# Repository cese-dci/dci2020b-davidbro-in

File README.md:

!!! important "Trabajo en progreso"
    Compruebe frecuentemente los cambios. Puedes aprovechar también 
    [**configurando las notificaciones de _release_**](https://docs.gitlab.com/ee/user/profile/notifications.html) 
    para [el repositorio](https://gitlab.com/FreeRTLS/FreeRTLS-Beacon/FreeRTLS-Beacon-Electronics) para estar enterado cuando 
    se realiza un nuevo lanzamiento.

# Bienvenido a FreeRTLS Beacon Electronics
**FreeRTLS Beacon Electronics** es una baliza UWB, _Open Source_, basada en el módulo
[DWM1001C](https://www.decawave.com/product/dwm1001-module/) de [Quorvo (antes Decawave)](https://www.decawave.com/). 

El desarrollo de este proyecto persigue los siguientes objetivos:

- Ser una versión de producción de [DWM1001 _development board_](https://www.decawave.com/product/dwm1001-development-board/)

Al igual que la original placa de desarrollo, posee las siguientes características[@dwm1001dev]:

- Soporte para UWB y _Bluetooth_
- Interfaz J-Link en la placa para grabar y depurar _firmware_
- Alimentación a través de micro USB

[Aquí](docs/requirements/index.md#por-que-hacerlo) se puede leer más sobre la motivación 
por la cuál se empezó con este proyecto.

La [documentación sobre la arquitectura](docs/architecture/index.md) permite entender cómo
está compuesto el sistema y cómo interactuán entre sí sus componentes. Cabe mencionar que 
**FreeRTLS Beacon Electronics** está formado por:

- Módulo [DWM1000C](https://www.decawave.com/product/dwm1001-module/)
- Interfaz J-Link implementada sobre 
[STM32F072CBTx](https://www.st.com/resource/en/datasheet/stm32f072c8.pdf)
- Fuente de alimentación a través de microUSB

### Misión
**FreeRTLS Beacon Electronics** busca permitir la implementación de sistemas de
localización en interiores, como es **FreeRTLS** pero no limitado a él. Es un _beacon_
UWB _open source_ y listo para fabricar o mejorar.

## Novedades
Para la lista completa de cambios visita el [control de cambios](CHANGELOG.md).

## ¿Cómo obtenerlo?
En la sección [_releases_](https://gitlab.com/FreeRTLS/FreeRTLS-Beacon/FreeRTLS-Beacon-Electronics/-/releases) del 
[repositorio](https://gitlab.com/FreeRTLS/FreeRTLS-Beacon/FreeRTLS-Beacon-Electronics) se pueden ver las versiones y el 
procedimiento para obtener **FreeRTLS Beacon Electronics**.

## ¿Cómo usarlo?
### Documentación
En la [documentación detallada](https://freertls.gitlab.io/FreeRTLS-Beacon/FreeRTLS-Beacon-Electronics) se encuentra todo
lo necesario para conocer cómo utilizar **FreeRTLS Beacon Electronics**.

## Contacto
Si quieres contactarme puedes hacerlo a davidmbroin@gmail.com.

## Licencia
Este proyecto usa la siguiente licencia: [CERN Open Hardware Licence Version 2 - Permissive](LICENSE.md).

\bibliography

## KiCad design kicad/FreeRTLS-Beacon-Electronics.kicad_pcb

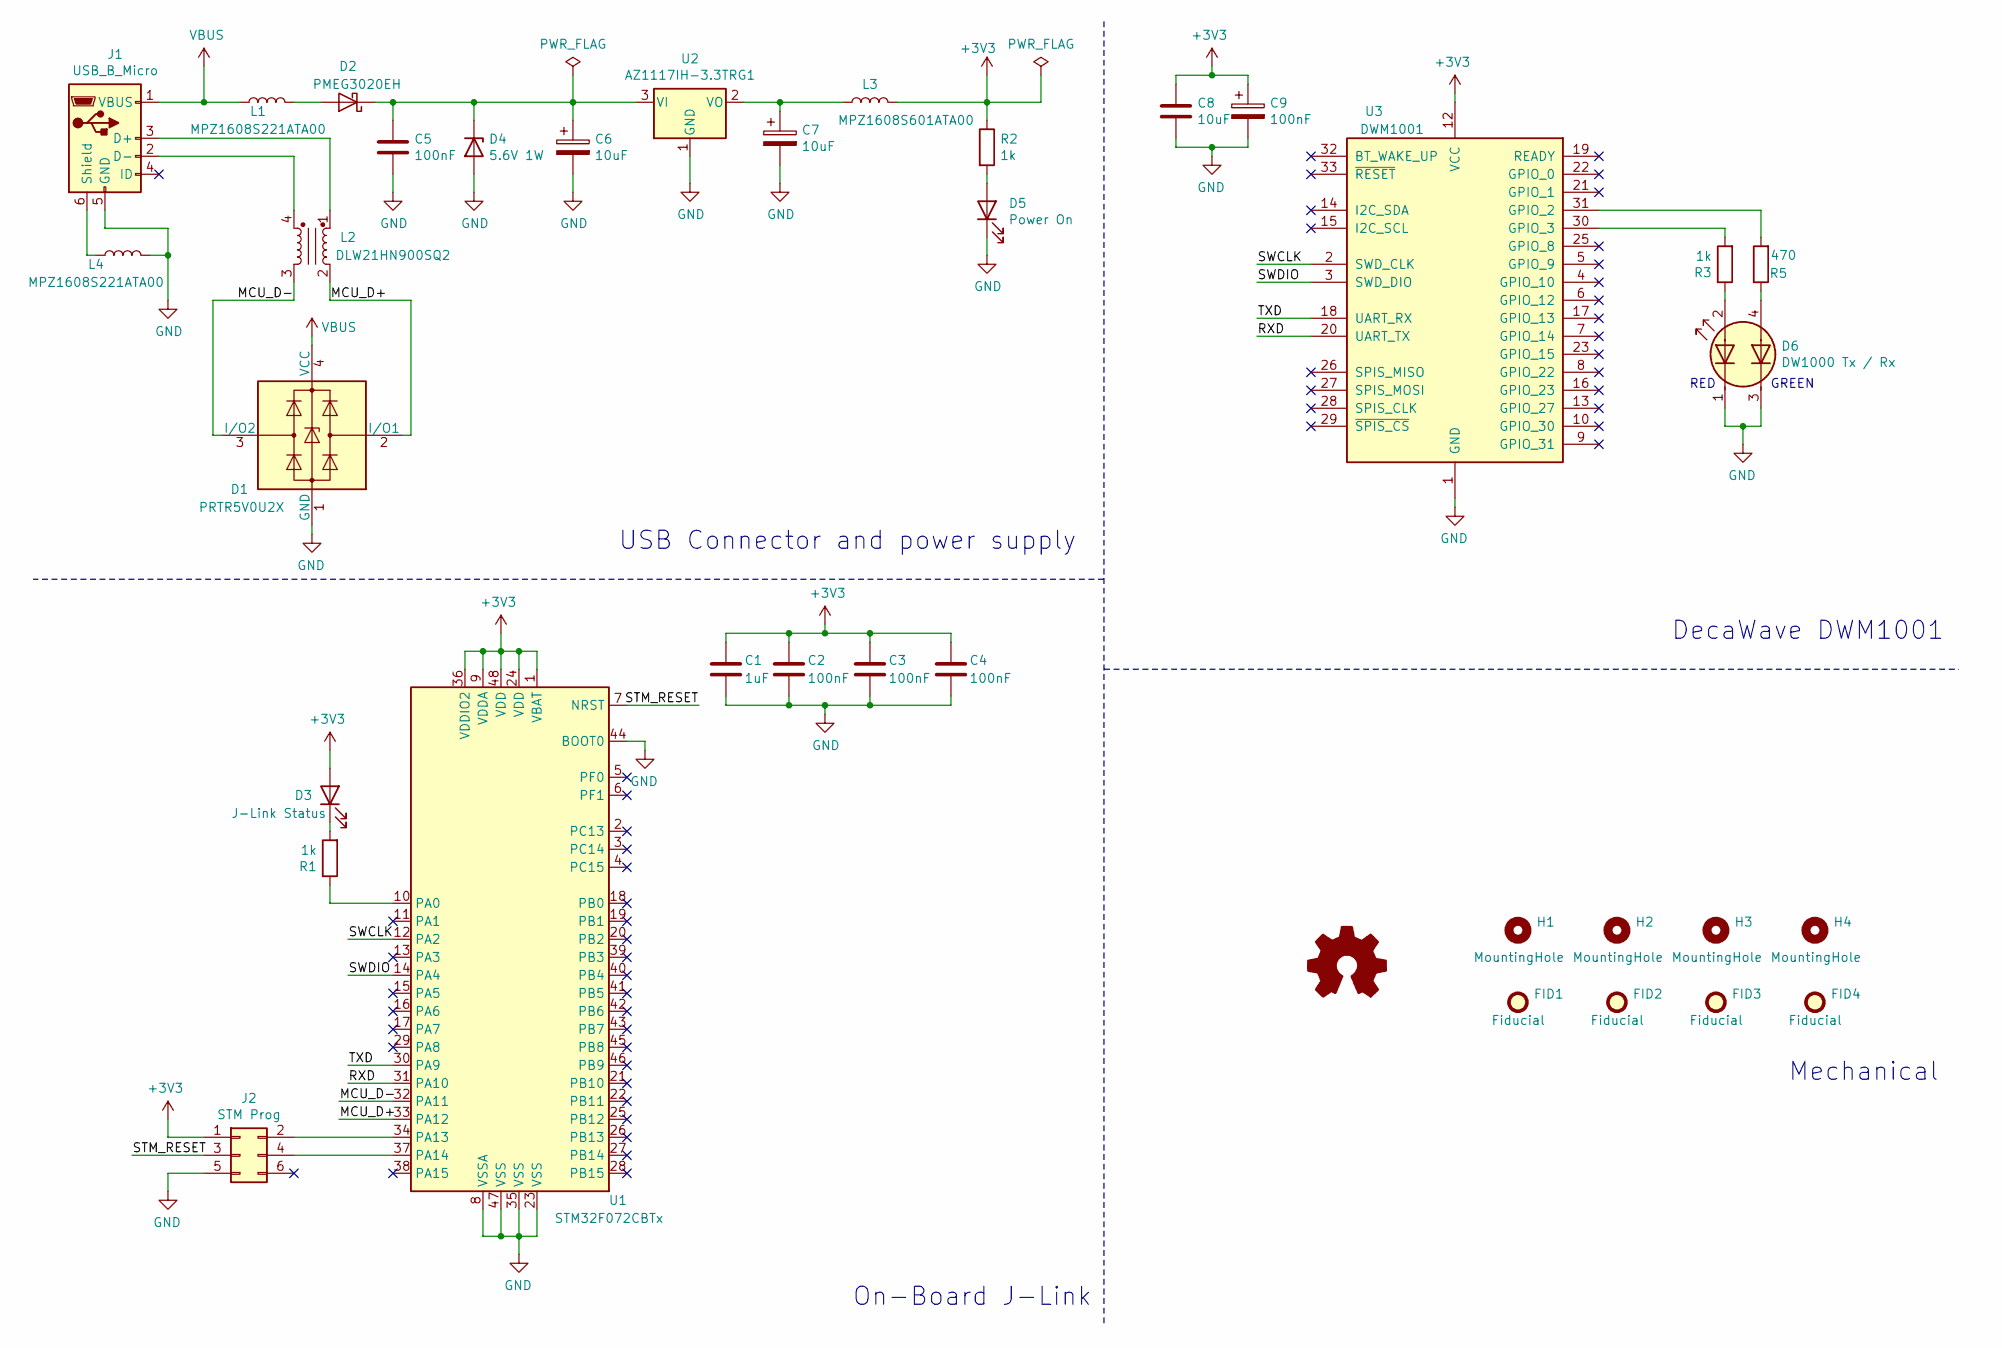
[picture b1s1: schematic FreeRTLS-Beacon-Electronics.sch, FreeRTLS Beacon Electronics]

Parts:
C1: 1uF; C_0603_1608Metric; MPN CL10A105KP8NNNC; Digi-Key_PN 1276-1182-1-ND
C2, C3, C4, C5, C9: 100nF; C_0603_1608Metric; MPN C0603C104Z3VACTU; Digi-Key_PN 399-1100-1-ND
C6, C7, C8: 10uF; C_0603_1608Metric; MPN C0603X6S100-106MNP; Digi-Key_PN 2679-C0603X6S100-106MNPTR-ND
D1: PRTR5V0U2X; SOT-143; MPN PRTR5V0U2X,215; Digi-Key_PN 1727-3884-1-ND
D2: PMEG3020EH; D_SOD-123F; MPN PMEG3020EH,115; Digi-Key_PN 1727-3873-1-ND
D3: J-Link Status; LED_0603_1608Metric; MPN 150060GS75000; Digi-Key_PN 732-4971-1-ND
D4: 5.6V 1W; D_SOD-123; MPN KDZVTFTR5.6B; Digi-Key_PN KDZVTFTR5.6BCT-ND
D5: Power On; LED_0603_1608Metric; MPN 150060RS75000; Digi-Key_PN 732-4978-1-ND
D6: DW1000 Tx / Rx; LED_L955QEQGC-TR_3.2x2.7mm_P1.7mm; MPN L955QEQGC-TR; Digi-Key_PN 2460-L955QEQGC-TR-ND
FID1, FID2, FID3, FID4: Fiducial; Fiducial_0.5mm_Mask1.5mm
H1, H2, H3, H4: MountingHole; MountingHole_3.2mm_M3
J1: USB_B_Micro; USB_Micro-B_Molex_47346-0001; MPN 0473460001; Digi-Key_PN WM17141CT-ND
J2: STM Prog; Tag-Connect_TC2030-IDC-FP_2x03_P1.27mm_Vertical
L1, L4: MPZ1608S221ATA00; L_0603_1608Metric; MPN MPZ1608S221ATA00; Digi-Key_PN 445-1565-1-ND
L2: DLW21HN900SQ2; FIL_DLW21HN900SQ2L; MPN DLW21HN900SQ2L; Digi-Key_PN 490-1064-1-ND
L3: MPZ1608S601ATA00; L_0603_1608Metric; MPN MPZ1608S601ATA00; Digi-Key_PN 445-2205-1-ND
LOGO1: Logo_Open_Hardware_Small; OSHW-Logo_5.7x6mm_SilkScreen
R1, R2, R3: 1k; R_0603_1608Metric; MPN RC0603JR-071KL; Digi-Key_PN 311-1.0KGRCT-ND
R5: 470; R_0603_1608Metric; MPN RC0603JR-07470RL; Digi-Key_PN 311-470GRCT-ND
U1: STM32F072CBTx; LQFP-48_7x7mm_P0.5mm; MPN STM32F072C8T6; Digi-Key_PN 497-17358-ND
U2: AZ1117IH-3.3TRG1; SOT-223-3_TabPin2; MPN AZ1117IH-3.3TRG1; Digi-Key_PN AZ1117IH-3.3TRG1DICT-ND
U3: DWM1001; DecaWave_DWM1001; MPN DWM1001C; Digi-Key_PN 1479-1004-1-ND

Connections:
+3V3: C1.1, C2.1, C3.1, C4.1, C8.1, C9.1, D3.2 (A), J2.1, L3.2, R2.1, U1.1 (VBAT), U1.9 (VDDA), U1.24 (VDD), U1.36 (VDDIO2), U1.48 (VDD), U3.12 (VCC)
/MCU_D+: D1.2 (I/O1), L2.2, U1.33 (PA12)
/MCU_D-: D1.3 (I/O2), L2.3, U1.32 (PA11)
/RXD: U1.31 (PA10), U3.20 (UART_TX)
/STM_RESET: J2.3, U1.7 (NRST)
/SWCLK: U1.12 (PA2), U3.2 (SWD_CLK)
/SWDIO: U1.14 (PA4), U3.3 (SWD_DIO)
/TXD: U1.30 (PA9), U3.18 (UART_RX)
GND: C1.2, C2.2, C3.2, C4.2, C5.2, C6.2, C7.2, C8.2, C9.2, D1.1 (GND), D4.2 (A), D5.1 (K), D6.1 (A1), D6.3 (A2), J1.5 (GND), J2.5, L4.2, U1.8 (VSSA), U1.23 (VSS), U1.35 (VSS), U1.44 (BOOT0), U1.47 (VSS), U2.1 (GND), U3.1 (GND), U3.11 (GND), U3.24 (GND), U3.34 (GND)
unnamed: C5.1, C6.1, D2.1 (K), D4.1 (K), U2.3 (VI)
unnamed: C7.1, L3.1, U2.2 (VO)
unnamed: D2.2 (A), L1.2
unnamed: D3.1 (K), R1.2
unnamed: D5.2 (A), R2.2
unnamed: D6.2 (K1), R3.1
unnamed: D6.4 (K2), R5.1
unnamed: J1.2 (D-), L2.4
unnamed: J1.3 (D+), L2.1
unnamed: J1.6 (Shield), L4.1
unnamed: J2.2, U1.34 (PA13)
unnamed: J2.4, U1.37 (PA14)
unnamed: R1.1, U1.10 (PA0)
unnamed: R3.2, U3.30 (GPIO_3)
unnamed: R5.2, U3.31 (GPIO_2)
VBUS: D1.4 (VCC), J1.1 (VBUS), L1.1

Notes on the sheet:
USB Connector and power supply
On-Board J-Link
DecaWave DWM1001
GREEN
RED
Mechanical

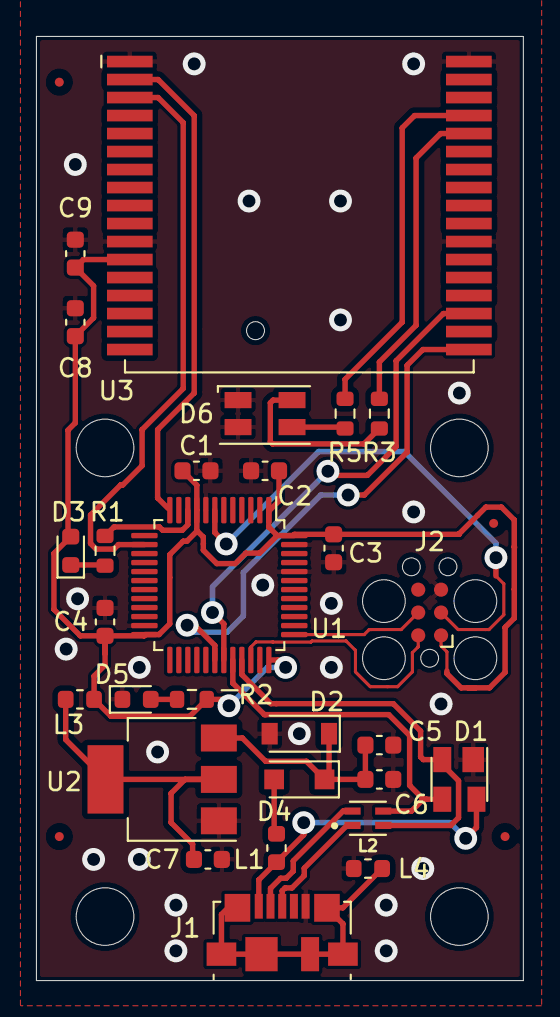
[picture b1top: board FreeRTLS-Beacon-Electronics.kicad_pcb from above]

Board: 2 copper layers, 27.1 x 52.5 mm, 37 parts (1 on the bottom side), 25 nets.

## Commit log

2020-08-12 Add README.md
2020-08-12 Add inital documentation files
2020-08-27 Add pcbops to CI config [skip ci]
2020-08-27 Add empty kicad files
2020-08-27 Try adding empty lib
2020-08-27 Add lib cache and set page settings
2020-08-27 Change revision to WIP!
2020-08-27 Modify CI config
2020-08-27 Add single quotes to avoid yml syntax error
2020-08-27 Add revision label and board edge
2020-08-27 Add page setting
2020-08-28 Add cnc_job
2020-08-28 Remove zip install and fix misspelling
2020-08-28 Add CI_PROJECT_DIR to script path
2020-08-28 Export variable instead of use variables node
2020-08-28 Try using flatcam in local dir
2020-08-28 Add trace to test cnc file generation
2020-08-28 Add via to test cnc file generation
2020-08-28 Change output directory
2020-08-28 Create output directory
2020-08-28 Update README.md, CHANGELOG.md, LICENSE.md files
2020-09-01 Add block_diagram.svg
2020-09-01 Add DWM USB and STM to sch
2020-09-02 Add STM32 connections
2020-09-02 Complete USB-STM connections
2020-09-02 Complete DWM1001 section
2020-09-02 Try moving pdf to docs folder
2020-09-02 Move bom to docs folder
2020-09-02 Embed pdf schematic
2020-09-02 Change size using style
2020-09-05 Copy mkdocs config from parent project
2020-09-05 Add workflow template
2020-09-05 Move workflow templat include to common.yml
2020-09-05 Add features to README
2020-09-05 Add requirements index and ref
2020-09-05 Add features index
2020-09-05 Fix features index
2020-09-05 Fix assets and add more
2020-09-05 Use single quotes
2020-09-05 Try just gitlab.com
2020-09-05 Try single quotes
2020-09-05 Uncomment jobs
2020-09-05 Add missing doc link
2020-09-05 Add details to README
2020-09-05 Remove unnecessary when: always
2020-09-08 New release syntax
2020-09-08 Fix misspelling variable
2020-09-12 Fix index reference
2020-09-17 Update README.md, docs/architecture/index.md files
2020-10-02 Add author and revisor to sch
2020-10-02 Fix bus usage to delimit components
2020-10-02 Annotate sch
2020-10-02 Add ferrite and change lib to fix ERC errors
2020-10-02 Add real lib and delete empty
2020-10-02 Update values and order power supply
2020-10-02 Add values and order labels
2020-10-02 Fill manufacturer data
2020-10-02 Assign footprints
2020-10-02 Add missing footprints and 3D models
2020-10-02 Add git ignore and fp libs table
2020-10-02 Remove ü and add .DS_Store to gitignore
2020-10-02 Add license info in page settings
2020-10-02 Add mounting holes and fiducials
2020-10-03 Fix lib path, change to relative
2020-10-09 Move LED to 3v3 to test whole power
2020-10-09 Enlarge and improve text
2020-10-09 Use value text to indicate usage
2020-10-09 Add dw1000 leds text
2020-10-10 Add pcb review MR template
2020-10-10 Fix misspelling in template
2020-10-10 Move when to rules
2020-10-10 Change to test CI
2020-10-10 Fix changes path
2020-10-15 Place all components and route some
2020-10-28 Finish routing
2020-10-28 Add 3d shapes
2020-11-03 Add PCBWay PCB Specification
2020-11-04 Add OSH logo
2020-11-04 Hide holes and fiducials refs
